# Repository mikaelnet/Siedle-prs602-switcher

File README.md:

# Siedle-prs602-switcher
Switching module for Siedle PRS602 programmer. 

This is a simple relay card built for Brf Albert that enables
programming of the three Siedle sections without physically
moving the programming cable.

## Function
One of the three sections can be selected either by a push on
one of the corresponding buttons on the case or by sending the
number 1-3 followed by a carrage return on the serial port. 

The relay card has a timeout of 10 minutes after it releases
the relays. The indicating leds blinks slowly two minutes before
the timeout and blinks rapidly one minute before the timeout.
A new 10 minute period is started if the active button or 
corresponding serial command is resent.

## Content
* schematic: Eagle schematic and board layout. The scematic is also expored as a pdf.
* arduino: A simple sketch for the Arduino firmware.
* case: STL files for the case for 3D printng.
* desktop: Simple Windows Form application for controlling the switch box

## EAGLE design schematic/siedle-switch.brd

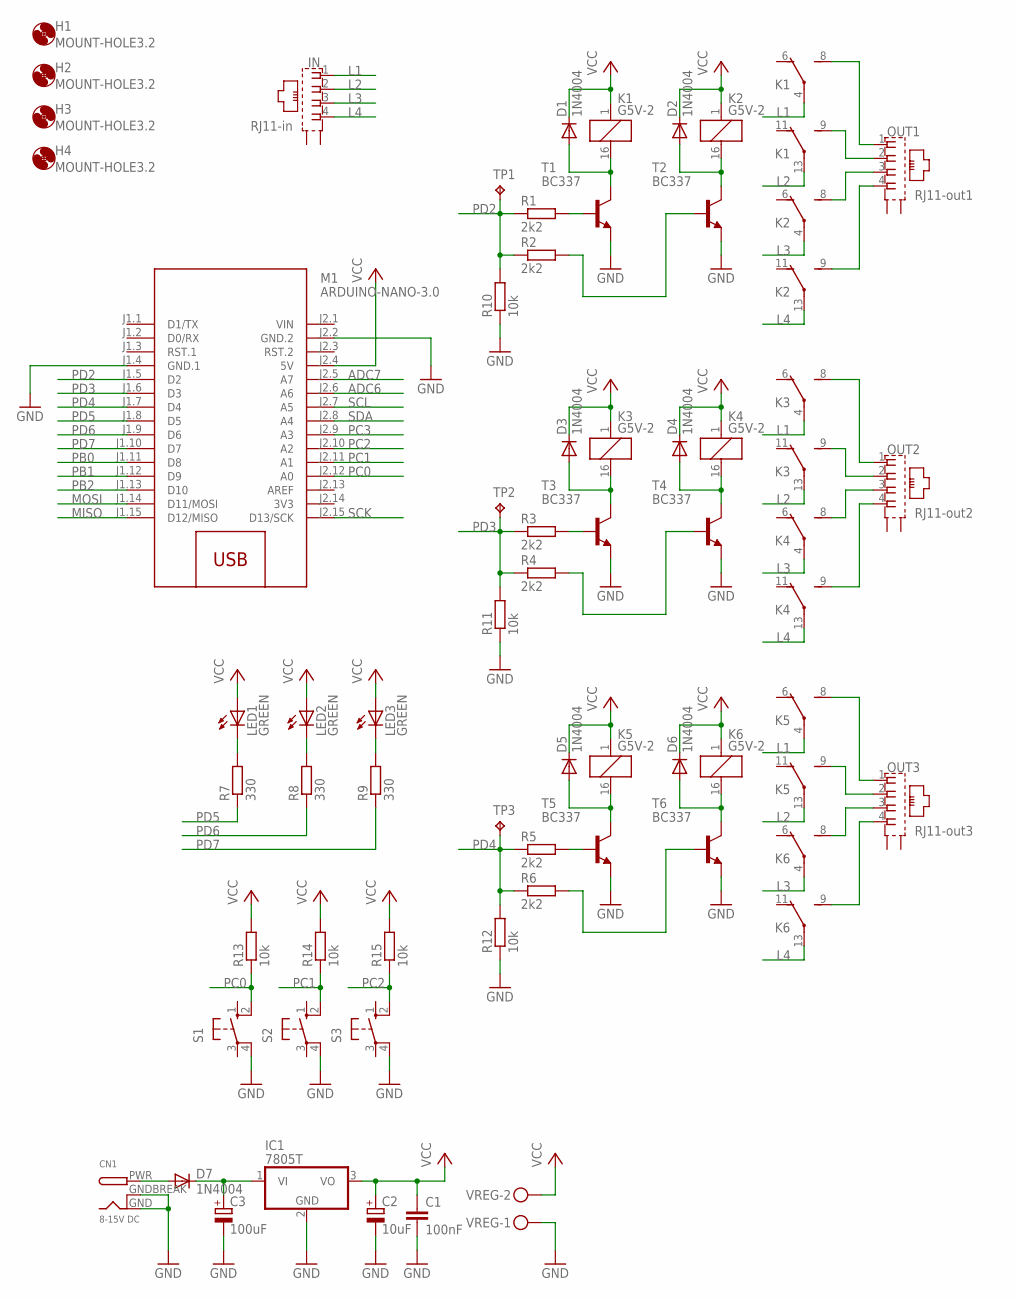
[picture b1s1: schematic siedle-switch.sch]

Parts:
C1: 100nF; C1206
C2: 10uF; E2,5-5
C3: 100uF; E3,5-8
CN1: 8-15V DC; DCJACK_2MM_PTH
D1, D2, D3, D4, D5, D6, D7: 1N4004; DO41-10
H1, H2, H3, H4: MOUNT-HOLE3.2; 3,2
IC1: 7805T; TO220H
IN: RJ11-in; XRJK-S-01-6-4-0-9M2
K1, K2, K3, K4, K5, K6: G5V-2
LED1, LED2, LED3: GREEN; LED3MM
M1: ARDUINO-NANO-3.0
OUT1: RJ11-out1; XRJK-S-01-6-4-0-9M2
OUT2: RJ11-out2; XRJK-S-01-6-4-0-9M2
OUT3: RJ11-out3; XRJK-S-01-6-4-0-9M2
R1, R2, R3, R4, R5, R6: 2k2; 0309/10
R7, R8, R9: 330; 0309/10
R10, R11, R12, R13, R14, R15: 10k; 0309/10
S1, S2, S3: 10-XX; B3F-10XX
T1, T2, T3, T4, T5, T6: BC337; TO92
TP1, TP2, TP3: TPPAD1-13; P1-13
VREG: MKDSN1,5/2-5,08

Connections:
3V3: M1.J2.14 (3V3)
ADC6: M1.J2.6 (A6)
ADC7: M1.J2.5 (A7)
GND: C1.2, C2.-, C3.-, CN1.GND, CN1.GNDBREAK, IC1.2 (GND), M1.J1.4 (GND.1), M1.J2.2 (GND.2), R10.1, R11.1, R12.1, S1.4 (P1), S2.4 (P1), S3.4 (P1), T1.1 (E), T2.1 (E), T3.1 (E), T4.1 (E), T5.1 (E), T6.1 (E), VREG.1
L1: IN.1, K1.4, K3.4, K5.4
L2: IN.2, K1.13, K3.13, K5.13
L3: IN.3, K2.4, K4.4, K6.4
L4: IN.4, K2.13, K4.13, K6.13
MISO: M1.J1.15 (D12/MISO)
MOSI: M1.J1.14 (D11/MOSI)
unnamed: D6.A, K6.16 (2), T6.3 (C)
unnamed: D5.A, K5.16 (2), T5.3 (C)
unnamed: R5.2, T5.2 (B)
unnamed: R6.2, T6.2 (B)
unnamed: K1.9 (S), OUT1.2
unnamed: K1.8 (S), OUT1.1
unnamed: K2.8 (S), OUT1.3
unnamed: K2.9 (S), OUT1.4
unnamed: D1.A, K1.16 (2), T1.3 (C)
unnamed: R1.2, T1.2 (B)
unnamed: LED3.K (C), R9.2
unnamed: D2.A, K2.16 (2), T2.3 (C)
unnamed: R2.2, T2.2 (B)
unnamed: K3.9 (S), OUT2.2
unnamed: K4.8 (S), OUT2.3
unnamed: K4.9 (S), OUT2.4
unnamed: K3.8 (S), OUT2.1
unnamed: K5.9 (S), OUT3.2
unnamed: K6.8 (S), OUT3.3
unnamed: K6.9 (S), OUT3.4
unnamed: K5.8 (S), OUT3.1
unnamed: R3.2, T3.2 (B)
unnamed: D3.A, K3.16 (2), T3.3 (C)
unnamed: D4.A, K4.16 (2), T4.3 (C)
unnamed: LED2.K (C), R8.2
unnamed: LED1.K (C), R7.2
unnamed: R4.2, T4.2 (B)
unnamed: CN1.PWR, D7.A
unnamed: C3.+, D7.C, IC1.1 (VI)
PB0: M1.J1.11 (D8)
PB1: M1.J1.12 (D9)
PB2: M1.J1.13 (D10)
PC0: M1.J2.12 (A0), R13.1, S1.2 (S1)
PC1: M1.J2.11 (A1), R14.1, S2.2 (S1)
PC2: M1.J2.10 (A2), R15.1, S3.2 (S1)
PC3: M1.J2.9 (A3)
PD2: M1.J1.5 (D2), R1.1, R2.1, R10.2, TP1.TP
PD3: M1.J1.6 (D3), R3.1, R4.1, R11.2, TP2.TP
PD4: M1.J1.7 (D4), R5.1, R6.1, R12.2, TP3.TP
PD5: M1.J1.8 (D5), R7.1
PD6: M1.J1.9 (D6), R8.1
PD7: M1.J1.10 (D7), R9.1
SCK: M1.J2.15 (D13/SCK)
SCL: M1.J2.7 (A5)
SDA: M1.J2.8 (A4)
VCC: C1.1, C2.+, D1.C, D2.C, D3.C, D4.C, D5.C, D6.C, IC1.3 (VO), K1.1, K2.1, K3.1, K4.1, K5.1, K6.1, LED1.A, LED2.A, LED3.A, M1.J2.4 (5V), R13.2, R14.2, R15.2, VREG.2
VIN: M1.J2.1 (VIN)

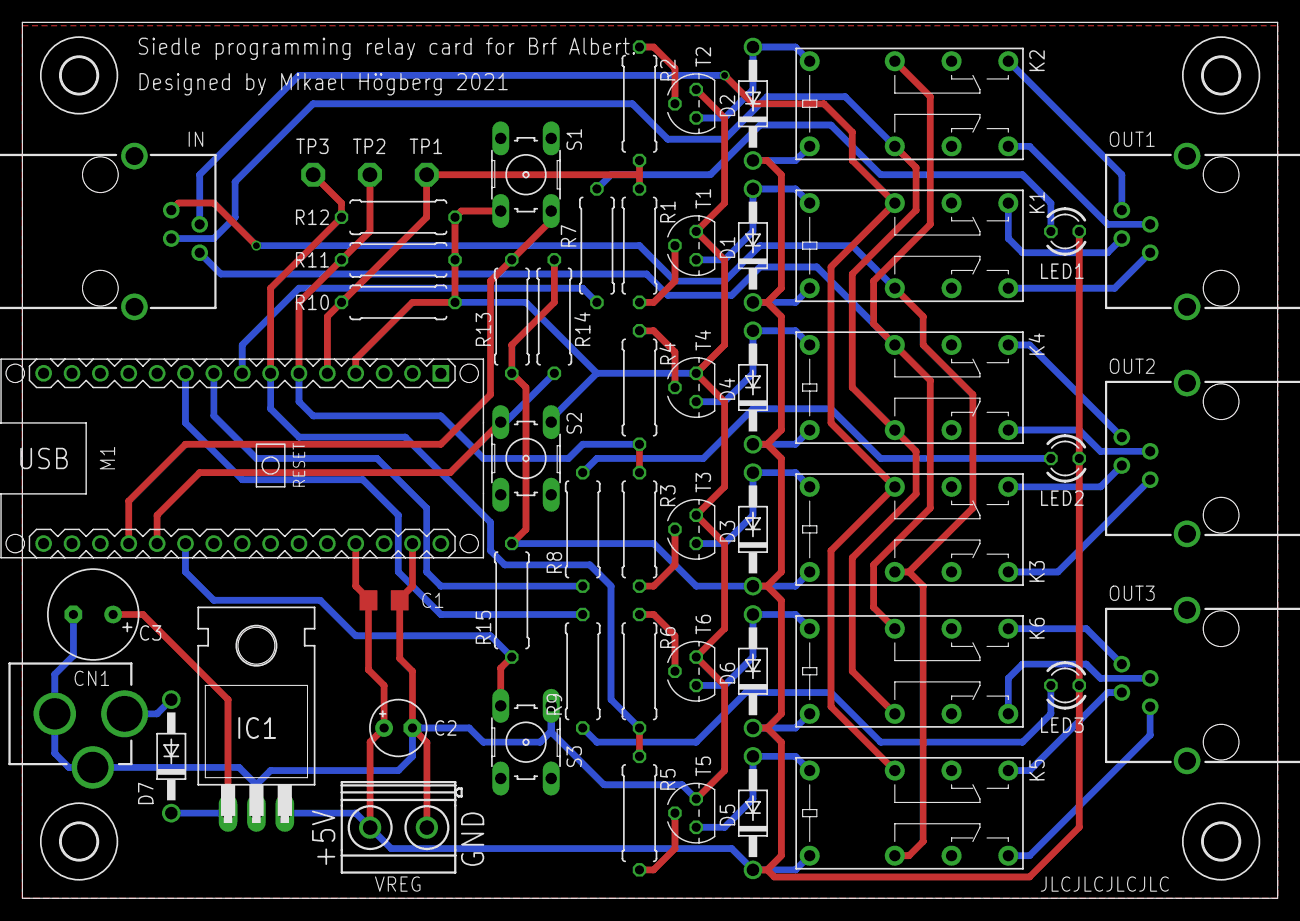
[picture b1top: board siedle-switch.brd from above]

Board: 4 copper layers, 112.4 x 78.4 mm, 58 parts (0 on the bottom side), 44 nets.

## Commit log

2021-02-14 schematic
2021-02-14 Arduino Nano firmware
2021-02-14 Case STL files
2021-02-14 git settings files
2021-02-14 desktop application
2021-02-14 Images
2021-02-14 Added BOM
2021-02-14 Added readme

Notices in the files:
parts and their libraries:
diy-modules: Released under the Creative Commons Attribution 4.0 International License: http://creativecommons.org/licenses/by/4.0
